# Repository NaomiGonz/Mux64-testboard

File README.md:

# Mux64-testboard

## The MUX64-Testboard is designed to monitor and test signals such as:
* Bias Voltage		&rarr; 	up to 1000V
* BPOL12V Output	&rarr; 	up to 1.2V 
* ETROC Output	&rarr; 	up to 1.2V
* LV input		&rarr;	up to 12V
* PTAT-BPOL12V	&rarr;	up to 2V
* VTRX+ RSSI Output	&rarr;	up to 2.5V 
* VTRX+ Power	&rarr;	up to 2.5V

## How It Works
Test signals would be inputs to the screw terminals. Their traces are then connected to the MUX64 chip which will be used to monitor their behavior. The select pins for the MUX64 come from the RB connector's digital pins. The output of the MUX64 is connected to a RB connector analog pin.

## Power 
The board is powered through the RB connectors bringing in ~9V which is then sent through a voltage regulator to convert into 1.2V which is then used to power the MUX64 chip. There is also a voltage reference for ~0.6V that is sent to a  MUX64 input, analog input on the RB connector, and is a test-point on the board.
<br>
<br>
## Versions
### v1.0
Modifications needed on physical board:
* Regultor has an added 100ohm resistor to have a constant load even when MUX64 is not connected (This change helps the regulator maintain a 1.2V output at all times)\
&nbsp; &nbsp; &nbsp; &nbsp; &nbsp; 
* A trace that started from the output of voltage divider was removed and reconnected to the input of the voltage divider. Also pins 5 and 6 of voltage regulator were shorted together (This changed the voltage refrence to now output ~0.6V and not 1.2V because the MUX64 and RB can only read voltages from 0-2V)

### v1.5
* updated physical fixes that were made after ordering first batch to be on new pcb layout and schematic\
&nbsp; &nbsp; &nbsp; &nbsp;

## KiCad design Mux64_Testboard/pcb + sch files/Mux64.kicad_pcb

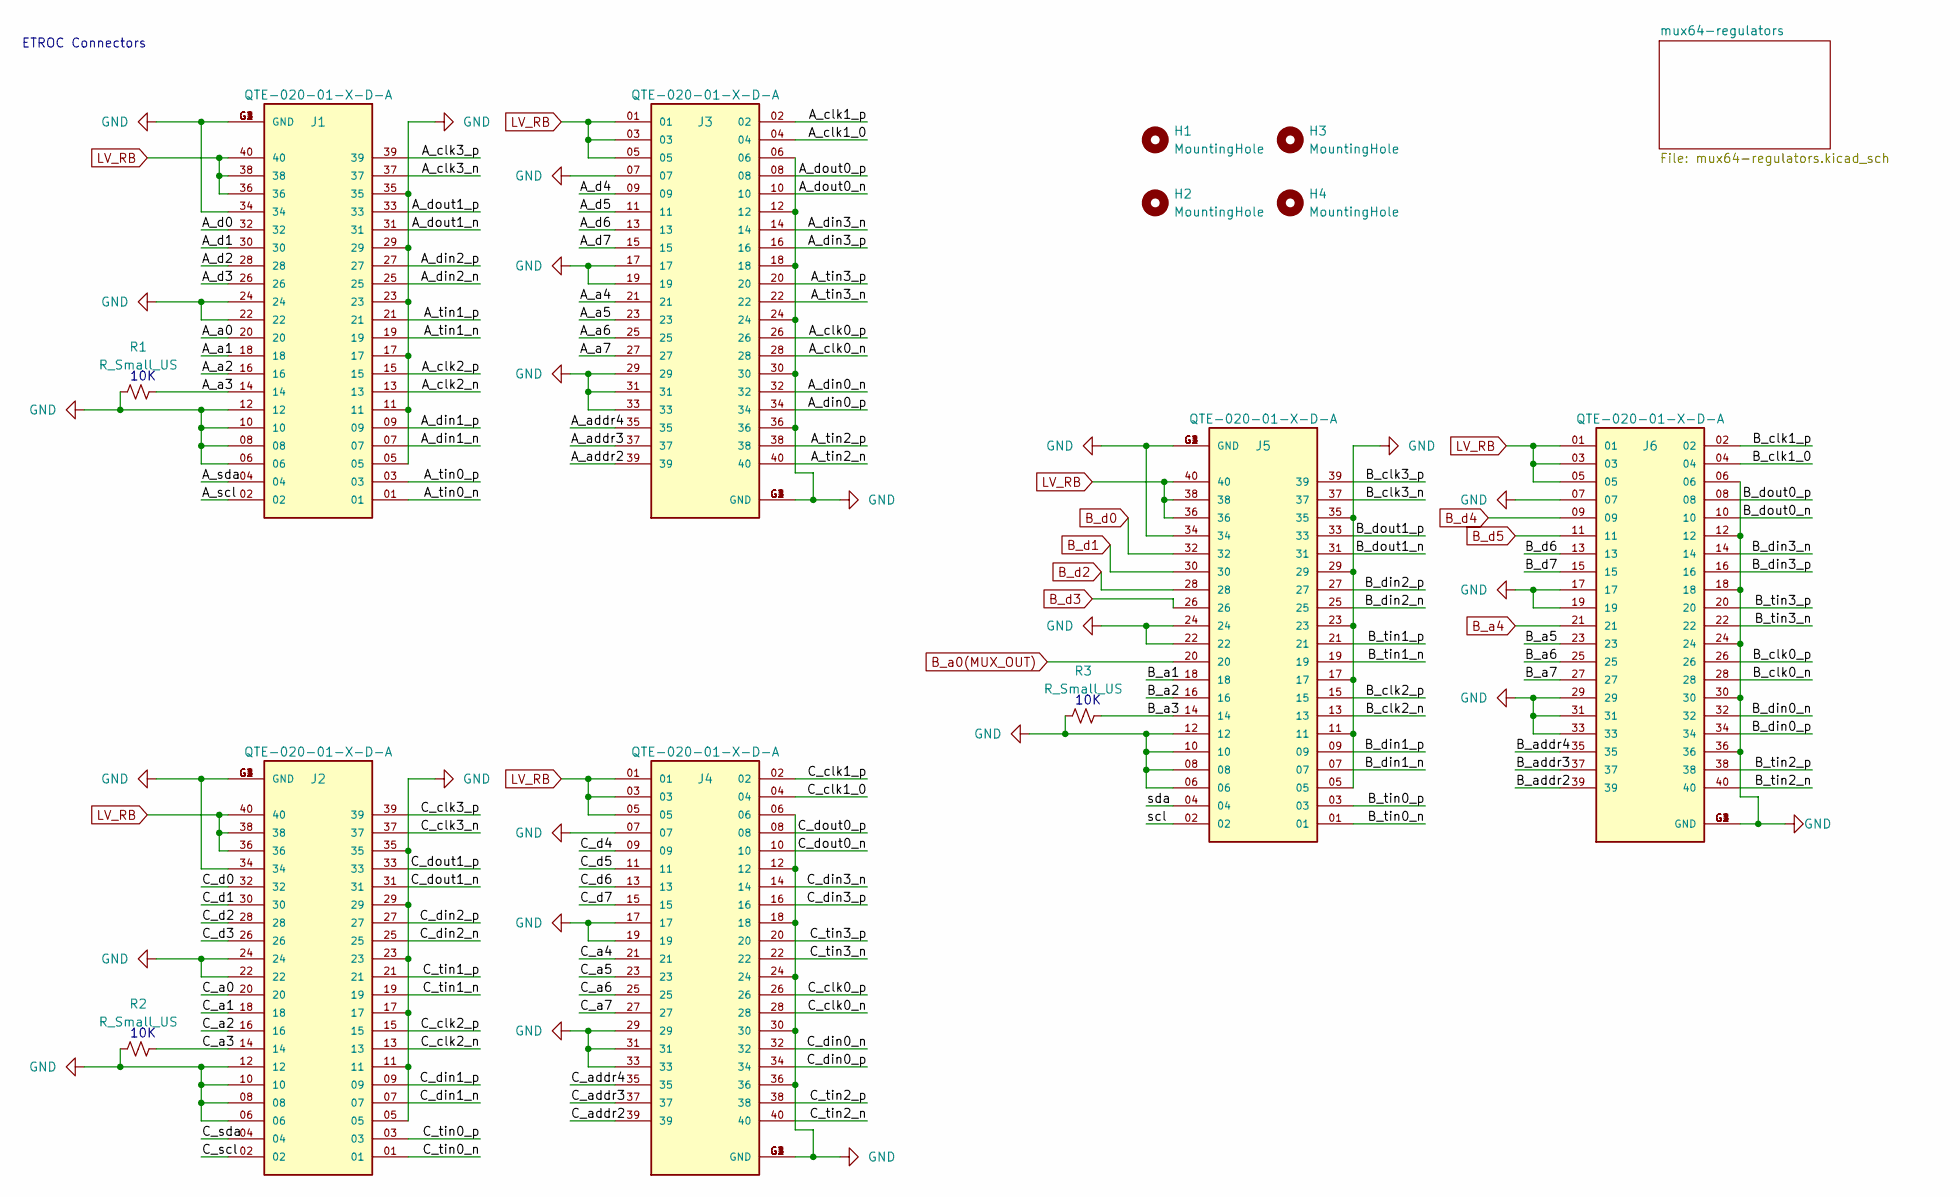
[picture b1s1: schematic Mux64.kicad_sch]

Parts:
H1, H2, H3, H4: MountingHole; MountingHole_2.5mm
J1, J2, J3, J4, J5, J6: QTE-020-01-X-D-A; SAMTEC_QTE-020-01-X-D-A; PARTREV K
R1, R2, R3: R_Small_US; R_0805_2012Metric

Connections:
/A_a0: J1.20
/A_a1: J1.18
/A_a2: J1.16
/A_a3: J1.14, R1.2
/A_a4: J3.21
/A_a5: J3.23
/A_a6: J3.25
/A_a7: J3.27
/A_addr2: J3.39
/A_addr3: J3.37
/A_addr4: J3.35
/A_clk0_n: J3.28
/A_clk0_p: J3.26
/A_clk1_0: J3.04
/A_clk1_p: J3.02
/A_clk2_n: J1.13
/A_clk2_p: J1.15
/A_clk3_n: J1.37
/A_clk3_p: J1.39
/A_d0: J1.32
/A_d1: J1.30
/A_d2: J1.28
/A_d3: J1.26
/A_d4: J3.09
/A_d5: J3.11
/A_d6: J3.13
/A_d7: J3.15
/A_din0_n: J3.32
/A_din0_p: J3.34
/A_din1_n: J1.07
/A_din1_p: J1.09
/A_din2_n: J1.25
/A_din2_p: J1.27
/A_din3_n: J3.14
/A_din3_p: J3.16
/A_dout0_n: J3.10
/A_dout0_p: J3.08
/A_dout1_n: J1.31
/A_dout1_p: J1.33
/A_scl: J1.02
/A_sda: J1.04
/A_tin0_n: J1.01
/A_tin0_p: J1.03
/A_tin1_n: J1.19
/A_tin1_p: J1.21
/A_tin2_n: J3.40
/A_tin2_p: J3.38
/A_tin3_n: J3.22
/A_tin3_p: J3.20
/B_a1: J5.18
/B_a2: J5.16
/B_a3: J5.14, R3.2
/B_a5: J6.23
/B_a6: J6.25
/B_a7: J6.27
/B_addr2: J6.39
/B_addr3: J6.37
/B_addr4: J6.35
/B_clk0_n: J6.28
/B_clk0_p: J6.26
/B_clk1_0: J6.04
/B_clk1_p: J6.02
/B_clk2_n: J5.13
/B_clk2_p: J5.15
/B_clk3_n: J5.37
/B_clk3_p: J5.39
/B_d6: J6.13
/B_d7: J6.15
/B_din0_n: J6.32
/B_din0_p: J6.34
/B_din1_n: J5.07
/B_din1_p: J5.09
/B_din2_n: J5.25
/B_din2_p: J5.27
/B_din3_n: J6.14
/B_din3_p: J6.16
/B_dout0_n: J6.10
/B_dout0_p: J6.08
/B_dout1_n: J5.31
/B_dout1_p: J5.33
/B_tin0_n: J5.01
/B_tin0_p: J5.03
/B_tin1_n: J5.19
/B_tin1_p: J5.21
/B_tin2_n: J6.40
/B_tin2_p: J6.38
/B_tin3_n: J6.22
/B_tin3_p: J6.20
/C_a0: J2.20
/C_a1: J2.18
/C_a2: J2.16
/C_a3: J2.14, R2.2
/C_a4: J4.21
/C_a5: J4.23
/C_a6: J4.25
/C_a7: J4.27
/C_addr2: J4.39
/C_addr3: J4.37
/C_addr4: J4.35
/C_clk0_n: J4.28
/C_clk0_p: J4.26
/C_clk1_0: J4.04
/C_clk1_p: J4.02
/C_clk2_n: J2.13
/C_clk2_p: J2.15
/C_clk3_n: J2.37
/C_clk3_p: J2.39
/C_d0: J2.32
/C_d1: J2.30
/C_d2: J2.28
/C_d3: J2.26
/C_d4: J4.09
/C_d5: J4.11
/C_d6: J4.13
/C_d7: J4.15
/C_din0_n: J4.32
/C_din0_p: J4.34
/C_din1_n: J2.07
/C_din1_p: J2.09
/C_din2_n: J2.25
/C_din2_p: J2.27
/C_din3_n: J4.14
/C_din3_p: J4.16
/C_dout0_n: J4.10
/C_dout0_p: J4.08
/C_dout1_n: J2.31
/C_dout1_p: J2.33
/C_scl: J2.02
/C_sda: J2.04
/C_tin0_n: J2.01
/C_tin0_p: J2.03
/C_tin1_n: J2.19
/C_tin1_p: J2.21
/C_tin2_n: J4.40
/C_tin2_p: J4.38
/C_tin3_n: J4.22
/C_tin3_p: J4.20
/scl: J5.02
/sda: J5.04
B_a0(MUX_OUT): J5.20; also elsewhere on the board
B_a4: J6.21; also elsewhere on the board
B_d0: J5.32; also elsewhere on the board
B_d1: J5.30; also elsewhere on the board
B_d2: J5.28; also elsewhere on the board
B_d3: J5.26; also elsewhere on the board
B_d4: J6.09; also elsewhere on the board
B_d5: J6.11; also elsewhere on the board
LV_RB: J1.36, J1.38, J1.40, J2.36, J2.38, J2.40, J3.01, J3.03, J3.05, J4.01, J4.03, J4.05, J5.36, J5.38, J5.40, J6.01, J6.03, J6.05; also elsewhere on the board
MUX64_A11: J1.05, J1.06, J1.08, J1.10, J1.11, J1.12, J1.17, J1.22, J1.23, J1.24, J1.29, J1.34, J1.35, J1.G1 (GND), J1.G2 (GND), J1.G3 (GND), J1.G4 (GND), J2.05, J2.06, J2.08, J2.10, J2.11, J2.12, J2.17, J2.22, J2.23, J2.24, J2.29, J2.34, J2.35, J2.G1 (GND), J2.G2 (GND), J2.G3 (GND), J2.G4 (GND), J3.06, J3.07, J3.12, J3.17, J3.18, J3.19, J3.24, J3.29, J3.30, J3.31, J3.33, J3.36, J3.G1 (GND), J3.G2 (GND), J3.G3 (GND), J3.G4 (GND), J4.06, J4.07, J4.12, J4.17, J4.18, J4.19, J4.24, J4.29, J4.30, J4.31, J4.33, J4.36, J4.G1 (GND), J4.G2 (GND), J4.G3 (GND), J4.G4 (GND), J5.05, J5.06, J5.08, J5.10, J5.11, J5.12, J5.17, J5.22, J5.23, J5.24, J5.29, J5.34, J5.35, J5.G1 (GND), J5.G2 (GND), J5.G3 (GND), J5.G4 (GND), J6.06, J6.07, J6.12, J6.17, J6.18, J6.19, J6.24, J6.29, J6.30, J6.31, J6.33, J6.36, J6.G1 (GND), J6.G2 (GND), J6.G3 (GND), J6.G4 (GND), R1.1, R2.1, R3.1; also elsewhere on the board

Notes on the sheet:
ETROC Connectors
10K

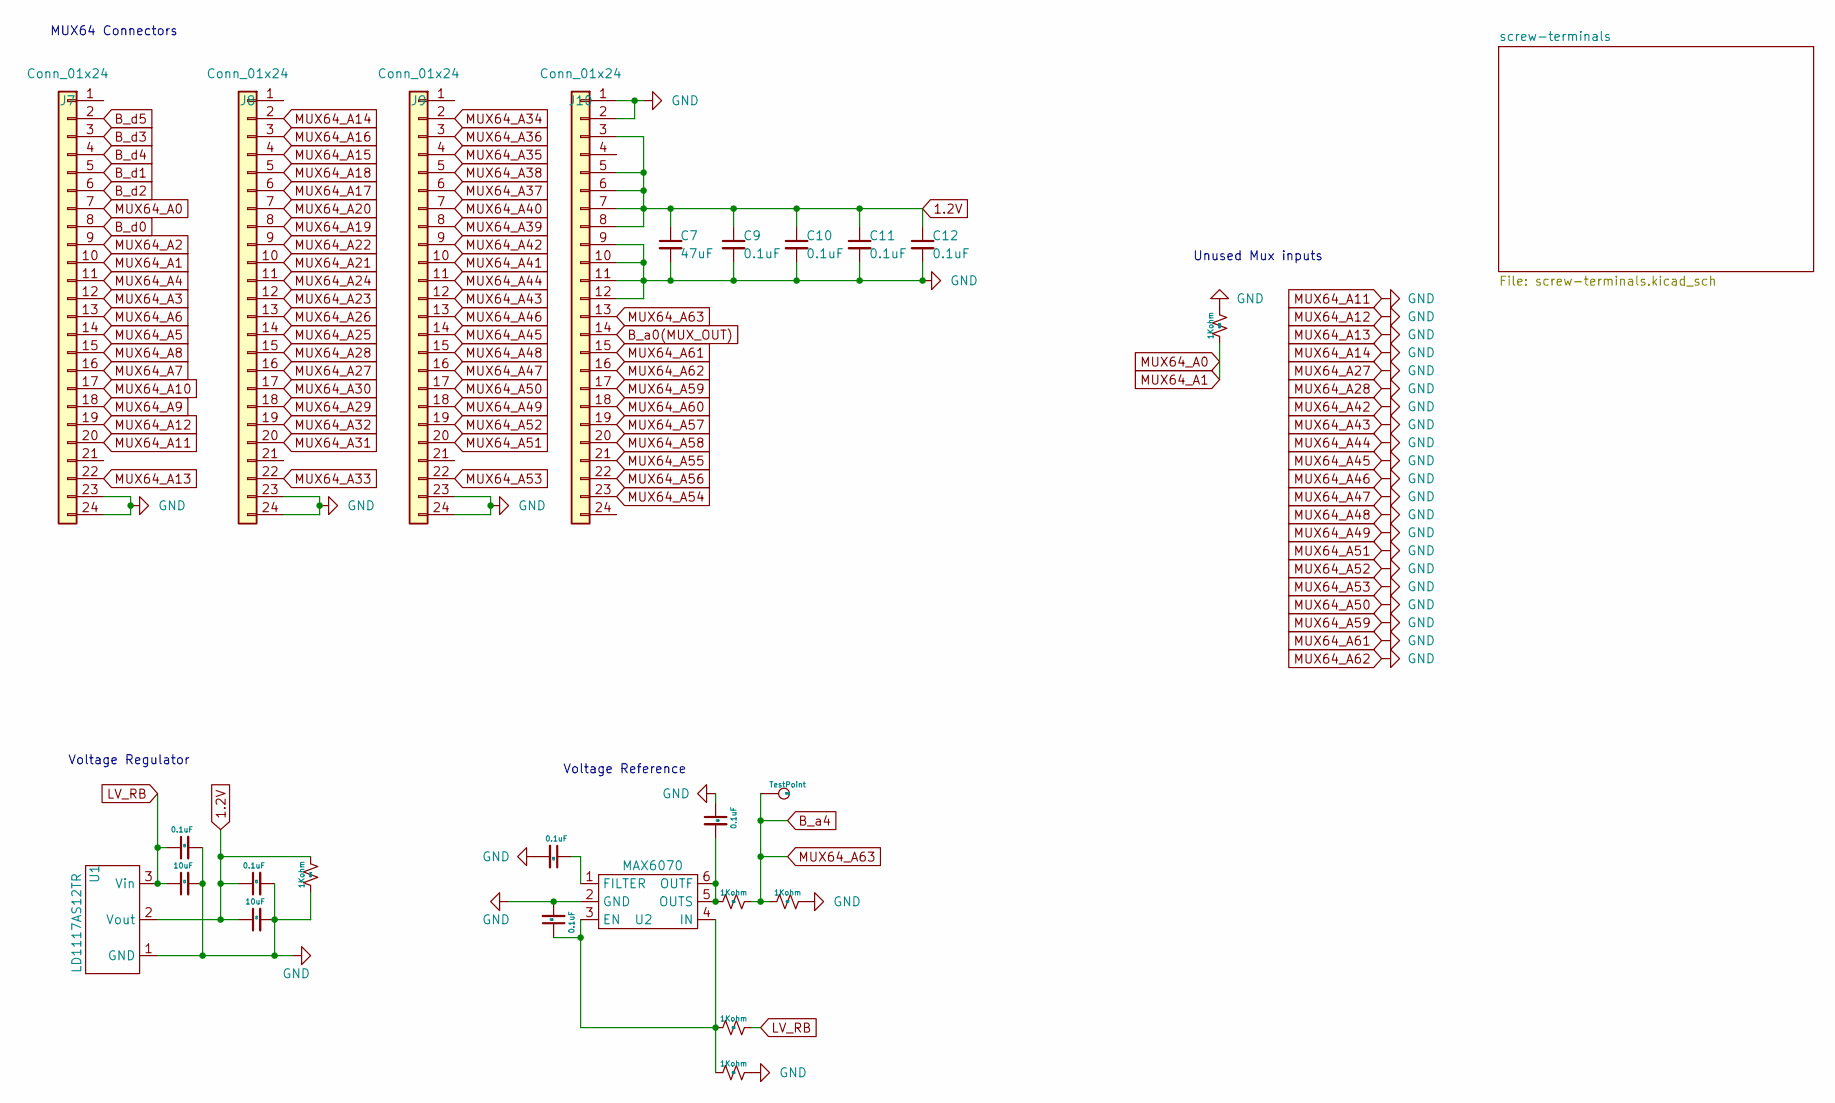
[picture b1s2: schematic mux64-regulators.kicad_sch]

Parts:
C1, C3, C5, C6, C8, C9, C10, C11, C12: 0.1uF; C_0805_2012Metric
C2, C4: 10uF; C_0805_2012Metric
C7: 47uF; C_0805_2012Metric
J7, J8, J9, J10: Conn_01x24; PinSocket_2x12_P2.54mm_Vertical
R4, R5, R6, R7, R23, R24: 1Kohm; R_0805_2012Metric
TP1: TestPoint; TestPoint_Pad_D2.5mm
U1: LD1117AS12TR; SOT-223-3_TabPin2
U2: MAX6070; SOT-23-6

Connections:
1.2V: C3.1, C4.1, C7.1, C9.1, C10.1, C11.1, C12.1, J10.3, J10.5, J10.6, J10.7, J10.8, R24.2, U1.2 (Vout)
B_a0(MUX_OUT): J10.14; also elsewhere on the board
B_a4: J10.13, R4.2, R7.1, TP1.1; also elsewhere on the board
B_d0: J7.8; also elsewhere on the board
B_d1: J7.5; also elsewhere on the board
B_d2: J7.6; also elsewhere on the board
B_d3: J7.3; also elsewhere on the board
B_d4: J7.4; also elsewhere on the board
B_d5: J7.2; also elsewhere on the board
LV_RB: C1.1, C2.1, R5.2, U1.3 (Vin); also elsewhere on the board
MUX64_A0: J7.7, J7.10, R23.1
MUX64_A2: J7.9; also elsewhere on the board
MUX64_A3: J7.12; also elsewhere on the board
MUX64_A4: J7.11; also elsewhere on the board
MUX64_A5: J7.14; also elsewhere on the board
MUX64_A6: J7.13; also elsewhere on the board
MUX64_A7: J7.16; also elsewhere on the board
MUX64_A8: J7.15; also elsewhere on the board
MUX64_A9: J7.18; also elsewhere on the board
MUX64_A10: J7.17; also elsewhere on the board
MUX64_A11: C1.2, C2.2, C3.2, C4.2, C5.2, C6.2, C7.2, C8.1, C9.2, C10.2, C11.2, C12.2, J7.19, J7.20, J7.22, J7.23, J7.24, J8.2, J8.15, J8.16, J8.23, J8.24, J9.9, J9.11, J9.12, J9.13, J9.14, J9.15, J9.16, J9.17, J9.18, J9.19, J9.20, J9.22, J9.23, J9.24, J10.1, J10.2, J10.9, J10.10, J10.11, J10.12, J10.15, J10.16, J10.17, R6.2, R7.2, R23.2, R24.1, U1.1 (GND), U2.2 (GND); also elsewhere on the board
MUX64_A15: J8.4; also elsewhere on the board
MUX64_A16: J8.3; also elsewhere on the board
MUX64_A17: J8.6; also elsewhere on the board
MUX64_A18: J8.5; also elsewhere on the board
MUX64_A19: J8.8; also elsewhere on the board
MUX64_A20: J8.7; also elsewhere on the board
MUX64_A21: J8.10; also elsewhere on the board
MUX64_A22: J8.9; also elsewhere on the board
MUX64_A23: J8.12; also elsewhere on the board
MUX64_A24: J8.11; also elsewhere on the board
MUX64_A25: J8.14; also elsewhere on the board
MUX64_A26: J8.13; also elsewhere on the board
MUX64_A29: J8.18; also elsewhere on the board
MUX64_A30: J8.17; also elsewhere on the board
MUX64_A31: J8.20; also elsewhere on the board
MUX64_A32: J8.19; also elsewhere on the board
MUX64_A33: J8.22; also elsewhere on the board
MUX64_A34: J9.2; also elsewhere on the board
MUX64_A35: J9.4; also elsewhere on the board
MUX64_A36: J9.3
MUX64_A37: J9.6; also elsewhere on the board
MUX64_A38: J9.5; also elsewhere on the board
MUX64_A39: J9.8; also elsewhere on the board
MUX64_A40: J9.7; also elsewhere on the board
MUX64_A41: J9.10; also elsewhere on the board
MUX64_A54: J10.23; also elsewhere on the board
MUX64_A55: J10.21; also elsewhere on the board
MUX64_A56: J10.22; also elsewhere on the board
MUX64_A57: J10.19; also elsewhere on the board
MUX64_A58: J10.20; also elsewhere on the board
MUX64_A60: J10.18; also elsewhere on the board
unnamed: C6.1, R5.1, R6.1, U2.3 (EN), U2.4 (IN)
unnamed: C5.1, U2.1 (FILTER)
unnamed: C8.2, R4.1, U2.5 (OUTS), U2.6 (OUTF)

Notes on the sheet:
Unused Mux inputs
Voltage Reference
Voltage Regulator
MUX64 Connectors

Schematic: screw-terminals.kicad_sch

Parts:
J11, J13, J14, J16, J17, J18: Screw_Terminal_01x12; TerminalBlock_Phoenix_MPT-0,5-12-2.54_1x12_P2.54mm_Horizont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
J12: Screw_Terminal_01x06; TerminalBlock_RND_205-00071_1x06_P7.50mm_Horizontal
R8, R9, R10, R15, R16, R17, R18, R19, R20, R39, R40, R41, R42, R43, R44, R45, R46, R47, R48, R49, R50, R57, R58, R59, R60, R61, R62, R64, R70, R71, R72, R73, R74, R81, R82, R83, R84, R85, R86, R87, R88, R89, R90, R91, R92, R93, R94, R95, R96, R97, R98, R99, R100, R101, R102, R103, R104, R105, R106, R107, R108, R109, R110: 82Kohm; R_0805_2012Metric
R11, R12, R13, R14, R21, R22: 50Mohm; R_1206_3216Metric
R27, R28, R29, R30, R31, R32: 240Kohm; R_0805_2012Metric
R51, R52, R53, R54, R55, R56: 1Mohm; R_0805_2012Metric

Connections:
/mux64-regulators/screw-terminals/HV0: J12.1, R14.2
/mux64-regulators/screw-terminals/HV1: J12.3, R21.2
/mux64-regulators/screw-terminals/HV2: J12.5, R22.2
MUX64_A2: R74.2, R86.1; also elsewhere on the board
MUX64_A3: R73.2, R85.1; also elsewhere on the board
MUX64_A4: R72.2, R84.1; also elsewhere on the board
MUX64_A5: R71.2, R83.1; also elsewhere on the board
MUX64_A6: R70.2, R82.1; also elsewhere on the board
MUX64_A7: R64.2, R81.1; also elsewhere on the board
MUX64_A8: R10.2, R13.1; also elsewhere on the board
MUX64_A9: R9.2, R12.1; also elsewhere on the board
MUX64_A10: R8.2, R11.1; also elsewhere on the board
MUX64_A11: J11.2, J11.4, J11.6, J11.8, J11.10, J11.12, J12.2, J12.4, J12.6, J13.2, J13.4, J13.6, J13.8, J13.10, J13.12, J14.2, J14.4, J14.6, J14.8, J14.10, J14.12, J16.2, J16.4, J16.6, J16.8, J16.10, J16.12, J17.2, J17.4, J17.6, J17.8, J17.10, J17.12, J18.2, J18.4, J18.6, J18.8, J18.10, J18.12, R8.1, R9.1, R10.1, R15.1, R16.1, R17.1, R18.1, R19.1, R20.1, R39.1, R40.1, R41.1, R42.1, R43.1, R44.1, R45.1, R46.1, R47.1, R48.1, R49.1, R50.1, R64.1, R70.1, R71.1, R72.1, R73.1, R74.1, R87.1, R88.1, R89.1, R90.1, R91.1, R92.1, R93.1, R94.1, R95.1, R96.1, R97.1, R98.1; also elsewhere on the board
MUX64_A15: R94.2, R106.1; also elsewhere on the board
MUX64_A16: R88.2, R105.1; also elsewhere on the board
MUX64_A17: R96.2, R108.1; also elsewhere on the board
MUX64_A18: R95.2, R107.1; also elsewhere on the board
MUX64_A19: R98.2, R110.1; also elsewhere on the board
MUX64_A20: R97.2, R109.1; also elsewhere on the board
MUX64_A21: R45.2, R56.1; also elsewhere on the board
MUX64_A22: R44.2, R55.1; also elsewhere on the board
MUX64_A23: R43.2, R54.1; also elsewhere on the board
MUX64_A24: R42.2, R53.1; also elsewhere on the board
MUX64_A25: R41.2, R52.1; also elsewhere on the board
MUX64_A26: R39.2, R51.1; also elsewhere on the board
MUX64_A29: R50.2, R62.1; also elsewhere on the board
MUX64_A30: R49.2, R61.1; also elsewhere on the board
MUX64_A31: R48.2, R60.1; also elsewhere on the board
MUX64_A32: R47.2, R59.1; also elsewhere on the board
MUX64_A33: R46.2, R58.1; also elsewhere on the board
MUX64_A34: R40.2, R57.1; also elsewhere on the board
MUX64_A35: R15.2, R27.1; also elsewhere on the board
MUX64_A37: R17.2, R29.1; also elsewhere on the board
MUX64_A38: R16.2, R28.1; also elsewhere on the board
MUX64_A39: R19.2, R31.1; also elsewhere on the board
MUX64_A40: R18.2, R30.1; also elsewhere on the board
MUX64_A41: R20.2, R32.1; also elsewhere on the board
MUX64_A54: R93.2, R104.1; also elsewhere on the board
MUX64_A55: R91.2, R102.1; also elsewhere on the board
MUX64_A56: R92.2, R103.1; also elsewhere on the board
MUX64_A57: R89.2, R100.1; also elsewhere on the board
MUX64_A58: R90.2, R101.1; also elsewhere on the board
MUX64_A60: R87.2, R99.1; also elsewhere on the board
unnamed: J11.1, R27.2
unnamed: J11.3, R28.2
unnamed: J11.5, R29.2
unnamed: J11.7, R30.2
unnamed: J11.9, R31.2
unnamed: J11.11, R32.2
unnamed: J13.1, R51.2
unnamed: J13.3, R52.2
unnamed: J13.5, R53.2
unnamed: J13.7, R54.2
unnamed: J13.9, R55.2
unnamed: J13.11, R56.2
unnamed: J14.1, R57.2
unnamed: J14.3, R58.2
unnamed: J14.5, R59.2
unnamed: J14.7, R60.2
unnamed: J14.9, R61.2
unnamed: J14.11, R62.2
unnamed: J16.1, R81.2
unnamed: J16.3, R82.2
unnamed: J16.5, R83.2
unnamed: J16.7, R84.2
unnamed: J16.9, R85.2
unnamed: J16.11, R86.2
unnamed: J17.1, R99.2
unnamed: J17.3, R100.2
unnamed: J17.5, R101.2
unnamed: J17.7, R102.2
unnamed: J17.9, R103.2
unnamed: J17.11, R104.2
unnamed: J18.1, R105.2
unnamed: J18.3, R106.2
unnamed: J18.5, R107.2
unnamed: J18.7, R108.2
unnamed: J18.9, R109.2
unnamed: J18.11, R110.2
unnamed: R11.2, R14.1
unnamed: R12.2, R21.1
unnamed: R13.2, R22.1

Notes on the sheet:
~2/25 Vin
~1/1250 Vin
1/2 Vin
1/4 Vin

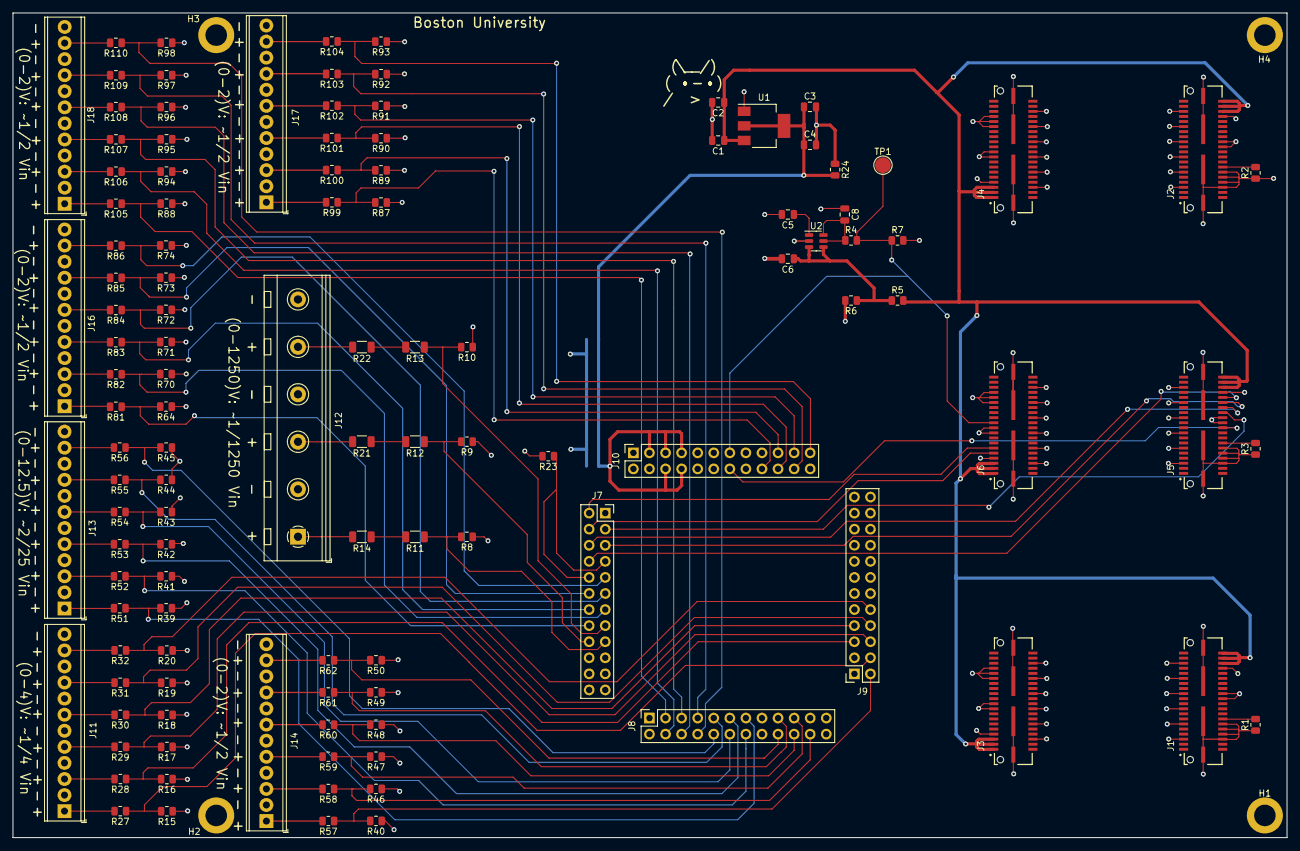
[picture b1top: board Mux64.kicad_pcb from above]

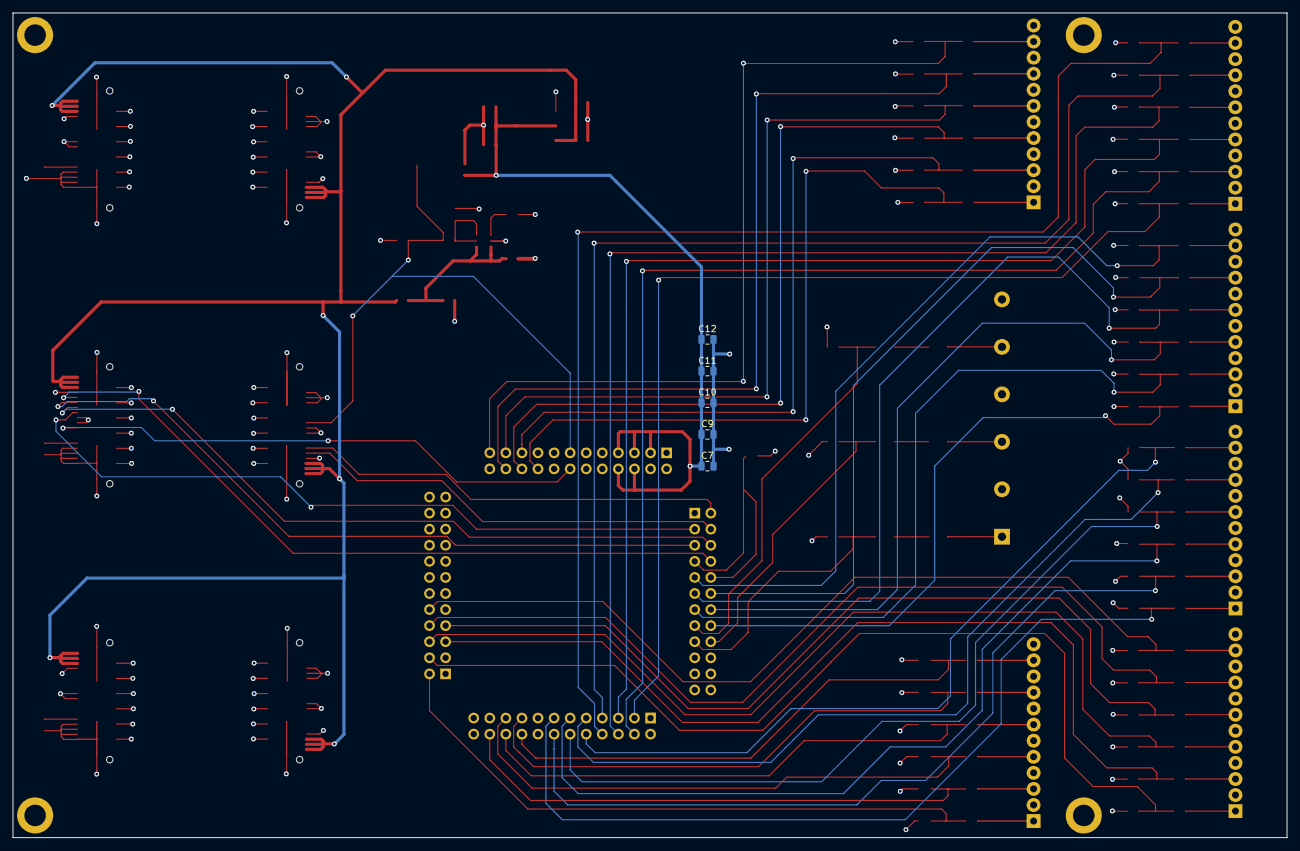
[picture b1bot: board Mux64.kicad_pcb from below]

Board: 4 copper layers, 201.3 x 130.3 mm, 126 parts (5 on the bottom side), 99 nets.

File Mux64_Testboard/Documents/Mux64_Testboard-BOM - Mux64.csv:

Source:,/Users/naomi_12/Desktop/Research/Mux64_Testboard/Mux64.kicad_sch,,,,,,,,,
Date:,"Tuesday, June 27, 2023 at 11:06:48 AM",,,,,,,,,
Tool:,Eeschema (6.0.11-0),,,,,,,,,
Generator:,/Applications/KiCad/KiCad.app/Contents/SharedSupport/plugins/bom_csv_grouped_by_value.py,,,,,,,,,
Component Count:,125,,,,,,,,,
,,,,,,,,,,
,,,,,,,,,,
,,,,,,,,,,
Collated Components:,,,,,,,,,,
,,,,,,,,,,
Qty per Board,Qty to Order,Reference(s),Value,LibPart,Footprint,Datasheet,MANUFACTURER,Indiv. Price,Group Price,Link to Buy Part
9,50,"C1, C3, C5, C6, C8, C9, C10, C11, C12",0.1uF,Device:C_Small,Capacitor_SMD:C_0805_2012Metric,https://www.digikey.com/en/products/detail/kemet/C0805C104J5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,KEMET,0.0764,3.82,https://www.digikey.com/en/products/detail/kemet/C0805C104J5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
2,50,"C2, C4",10uF,Device:C_Small,Capacitor_SMD:C_0805_2012Metric,https://connect.kemet.com:7667/gateway/IntelliData-Component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,KEMET,0.0584,2.92,https://www.digikey.com/en/products/detail/kemet/C0805C106K8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
1,10,C7,47uF,Device:C_Small,Capacitor_SMD:C_0805_2012Metric,https://www.mouser.com/datasheet/2/281/1/GRM21BC80G476ME15_0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,Murata,0.216,2.16,https://www.mouser.com/ProductDetail/81-GRM21BC80G476ME5L
4,~,"H1, H2, H3, H4",MountingHole,Mechanical:MountingHole,MountingHole:MountingHole_2.5mm,~,~,~,,~
6,40,"J1, J2, J3, J4, J5, J6",QTE-020-01-X-D-A,QTE-020-01-X-D-A:QTE-020-01-X-D-A,QTE-020-01-X-D-A:SAMTEC_QTE-020-01-X-D-A,http://suddendocs.samtec.com/prints/qte-xxx-xx-xxx-d-xxx-foo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,Samtec,9.15375,366.15,https://www.digikey.com/en/products/detail/samtec-inc/QTE-02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
4,24,"J7, J8, J9, J10",Conn_01x24,Connector_Generic:Conn_01x24,Connector_PinSocket_2.54mm:PinSocket_2x12_P2.54mm_Vertical,https://media.digikey.com/pdf/Data%20Sheets/Sullins%20PDFs/F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,Sullins Connector Solutions,1.269,30.46,https://www.digikey.com/en/products/detail/sullins-connector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
6,40,"J11, J13, J14, J16, J17, J18",Screw_Terminal_01x12,Connector:Screw_Terminal_01x12,"TerminalBlock_Phoenix:TerminalBlock_Phoenix_MPT-0,5-12-2.54_1x12_P2.54mm_Horizontal",https://www.phoenixcontact.com/en-us/products/printed-circui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,Phoenix Contact,9.77,390.8,https://www.mouser.com/ProductDetail/651-1725753
1,8,J12,Screw_Terminal_01x06,Connector:Screw_Terminal_01x06,TerminalBlock_RND:TerminalBlock_RND_205-00071_1x06_P7.50mm_Horizontal,https://www.phoenixcontact.com/en-us/products/printed-circui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,Phoenix Contact,4.96,39.68,https://www.mouser.com/ProductDetail/651-1988147
3,20,"R1, R2, R3",10Kohm,Device:R_Small_US,Resistor_SMD:R_0805_2012Metric,https://www.yageo.com/upload/media/product/productsearch/dat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,YAGEO,0.025,0.5,https://www.digikey.com/en/products/detail/yageo/RC0805FR-07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
5,100,"R4, R5, R6, R7, R23",1Kohm,Device:R_Small_US,Resistor_SMD:R_0805_2012Metric,https://www.yageo.com/upload/media/product/productsearch/dat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,YAGEO,0.0127,1.27,https://www.digikey.com/en/products/detail/yageo/RC0805FR-10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
63,500,"R8, R9, R10, R15, R16, R17, R18, R19, R20, R39, R40, R41, R42, R43, R44, R45, R46, R47, R48, R49, R50, R57, R58, R59, R60, R61, R62, R64, R70, R71, R72, R73, R74, R81, R82, R83, R84, R85, R86, R87, R88, R89, R90, R91, R92, R93, R94, R95, R96, R97, R98, R99, R100, R101, R102, R103, R104, R105, R106, R107, R108, R109, R110",82Kohm,Device:R_Small_US,Resistor_SMD:R_0805_2012Metric,https://www.yageo.com/upload/media/product/productsearch/dat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,Panasonic EC,0.0656,32.8,https://www.digikey.com/en/products/detail/yageo/RC0805JR-07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
6,50,"R11, R12, R13, R14, R21, R22",50Mohm,Device:R_Small_US,Resistor_SMD:R_1206_3216Metric,https://www.seielect.com/catalog/sei-hmc.pdf,Stackpole Electronics,2.7144,135.72,https://www.digikey.com/en/products/detail/stackpole-electro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
6,50,"R27, R28, R29, R30, R31, R32",240Kohm,Device:R_Small_US,Resistor_SMD:R_0805_2012Metric,https://www.yageo.com/upload/media/product/productsearch/dat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,YAGEO,0.0152,0.76,https://www.digikey.com/en/products/detail/yageo/RC0805FR-07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
6,50,"R51, R52, R53, R54, R55, R56",1Mohm,Device:R_Small_US,Resistor_SMD:R_0805_2012Metric,https://www.te.com/usa-en/product-7-2176238-0.datasheet.pdf,TE connectivity ,0.2852,14.26,https://www.digikey.com/en/products/detail/te-connectivity-p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
1,~,TP1,TestPoint,Connector:TestPoint,TestPoint:TestPoint_Pad_D2.5mm,~,~,~,~,~
1,10,U1,LD1117AS12TR,Regulator_Linear:LD1117AS12TR,Package_TO_SOT_SMD:SOT-223-3_TabPin2,https://www.st.com/content/ccc/resource/technical/document/d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,STMicroelctronics,0.807,8.07,https://www.digikey.com/en/products/detail/stmicroelectronic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
1,10,U2,MAX6070,Reference_Voltage:MAX6070,Package_TO_SOT_SMD:SOT-23-6,https://www.analog.com/media/en/technical-documentation/data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,Analog Devices,2.499,24.99,https://www.digikey.com/en/products/detail/analog-devices-in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
,,,,,,,,,,
Parts Total Cost:,1054.36,,,,,,,,,
Digikeys Cart:,https://www.digikey.com/short/p3pc7tcv,,,,,,,,,
Mouser Cart:,https://www.mouser.com/ProjectManager/ProjectDetail.aspx?Acc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,,,,,,,,,
,Access ID:,84a895b1e6,,,,,,,,
JLCPCB,https://cart.jlcpcb.com/shopcart/cart?_ga=2.126180936.495096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,,,,,,,,,
PCB Cost:,50.7,,,,,,,,,
,,,,,,,,,,
Total Cost:,1105.06,,,,,,,,,

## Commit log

2023-06-06 Final revision
    Fixed high voltage spacial issue and distributed traces to have less density on the bottom of the board
2023-06-07 Added +/-
    Made silkscreen more visible
2023-06-08 Added Gerber files
2023-06-11 Power and Ground traces resized
2023-06-16 Resolved DRC errors
2023-06-16 removed older files
2023-06-16 Fixed image path
2023-07-12 Delete Mux64/Schematics directory
    Changing format
2023-07-12 Delete Mux64/PCB directory
    changing format
2023-07-12 Delete Mux64/gerbers directory
    changing format
2023-07-12 Change layout
2023-07-12 Added images for readme
2023-07-24 Update README.md to explain physical modification
2023-07-24 Update README.md headings
2023-07-24 Added images of physical board changes
    physical changes from batch order from version 1v0
2023-07-24 Update README.md image
    change image
2023-07-24 Update README.md fromating
2023-07-24 Made improvements on v1.0
    Added a 100Ohm load to voltage regulator. Fixed wiring with voltage reference
2023-08-23 Completed v2
